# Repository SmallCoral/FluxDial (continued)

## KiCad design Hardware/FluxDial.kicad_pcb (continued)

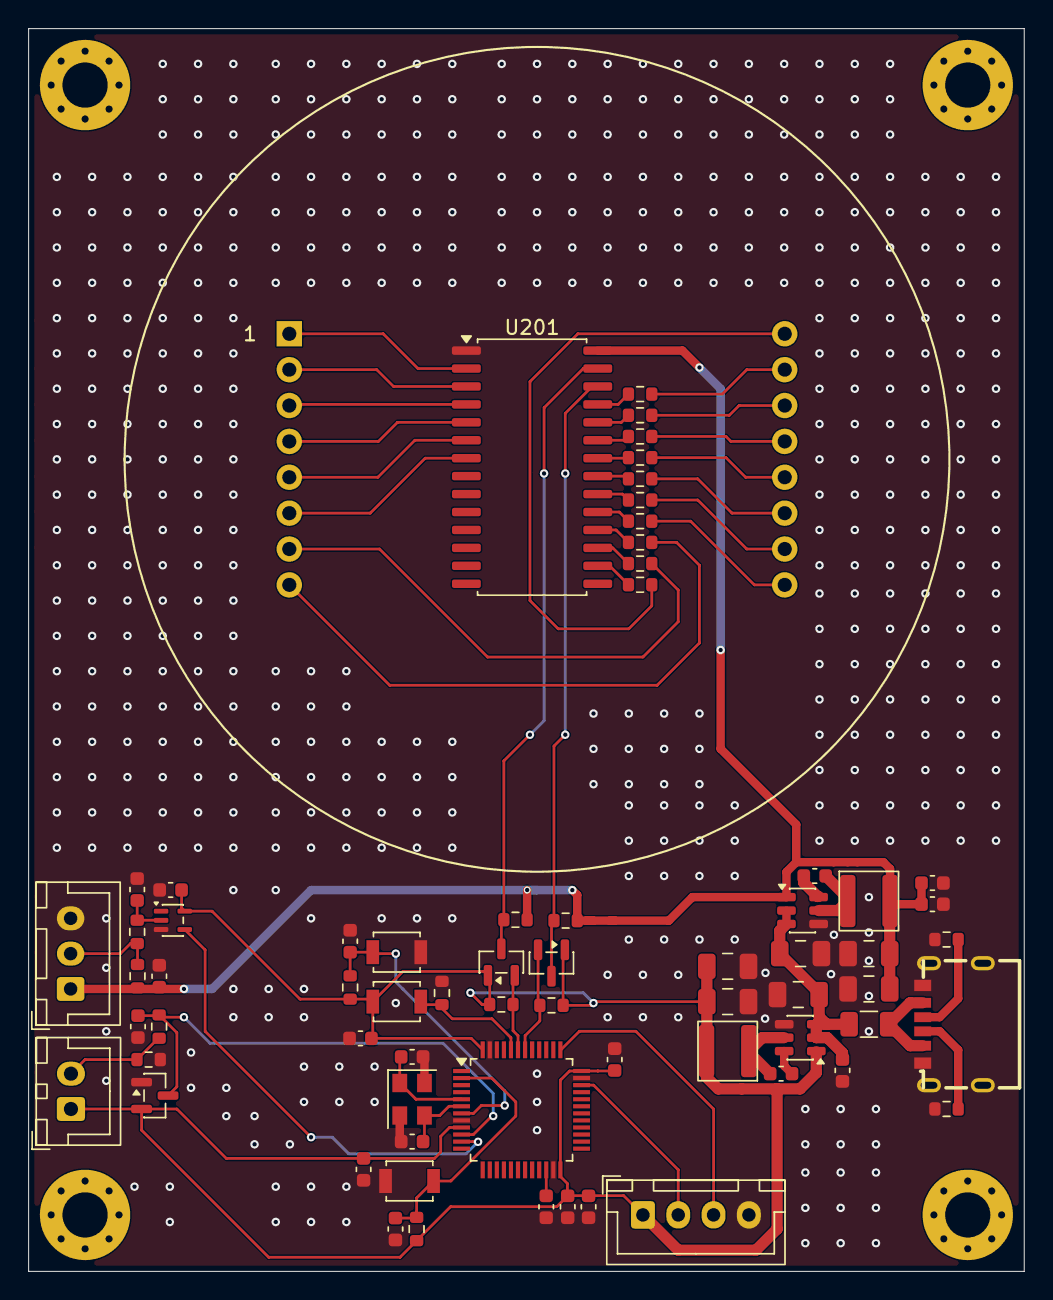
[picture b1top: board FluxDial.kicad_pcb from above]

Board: 2 copper layers, 70.5 x 88.0 mm, 68 parts (0 on the bottom side), 54 nets.

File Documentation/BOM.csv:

位号,数量,参数/型号,KiCad封装,采购与核对要求
J101,1,SHOU HAN TYPE-C 6P(073),FluxDial:Connector_USB__SHOU_HAN_TYPE-C-6P-073_C668623,SHOU HAN TYPE-C 6P(073)；LCSC C668623；仅供电无D+/D−；5V/3A资料额定；四个外侧椭圆屏蔽壳焊盘；无中间圆形定位孔；禁止从J101输入12V
J102,1,SWD / XH 2.50mm,FluxDial:Connector_JST__JST_XH_B4B-XH-A_1x04_P2.50mm_Vertical,JST B4B-XH-A立式4P；1=VREF/3.3V、2=SWDIO、3=SWCLK、4=GND；VREF仅作目标电压检测；接口不含NRST
F101,1,0.5A / 24V 保持电流,FluxDial:Fuse__Fuse_1206_3216Metric,Littelfuse 1206L050/24WR 或等效；保持电流0.5A；最大工作电压至少24V；核对温度降额
U101,1,AP63203WU-7,FluxDial:Package_TO_SOT_SMD__SOT-23-6,Diodes AP63203WU-7；固定3.3V；TSOT26；输入3.8～32V；靠近L101/C102/C106/C103/C105布局
U102,1,AP63205WU-7,FluxDial:Package_TO_SOT_SMD__SOT-23-6,Diodes AP63205WU-7；固定5V；TSOT26；输入3.8～32V；5V输入时工作于低压差模式；靠近L102/C110/C109/C107/C108布局
L101,1,3.9u / SWPA4030S3R9MT,FluxDial:Inductor_Sunlord_SWPA4030S,屏蔽功率电感；Isat最小3.0A；DCR最大74mΩ；用于3.3V DCDC
L102,1,4.7u / SWPA4030S4R7MT,FluxDial:Inductor_Sunlord_SWPA4030S,屏蔽功率电感；Isat最小2.9A；DCR最大78mΩ；用于5V DCDC
C101,1,100n / 25V,FluxDial:Capacitor_SMD__C_0603_1608Metric,0603英制/1608公制；≥25V；X7R；10%；输入高频旁路
"C102,C110",2,10u / 35V,FluxDial:Capacitor_SMD__C_1206_3216Metric,1206英制/3216公制；≥35V；X7R；10%；每路DCDC各一只就近输入储能；核对12V偏压下有效容量
"C103,C105,C107,C108",4,22u / 10V,FluxDial:Capacitor_SMD__C_1206_3216Metric,1206英制/3216公制；≥10V；X7R；10%；每路DCDC各两只；核对偏压下有效容量
"C106,C109",2,100n,FluxDial:Capacitor_SMD__C_0603_1608Metric,0603英制/1608公制；≥25V；X7R；DCDC自举电容，紧贴BST与SW引脚
"R101,R102",2,5.1k 1%,FluxDial:Resistor_SMD__R_0603_1608Metric,0603英制/1608公制；1%；额定功率≥0.1W
SW101,1,启动（BOOT）,FluxDial:Button_Switch_SMD__SW_SPST_B3U-1000P,Omron B3U-1000P；LCSC C231329；3.0×2.5mm；高1.6mm；常开瞬时
"R103,R104,R303,R305",4,10k,FluxDial:Resistor_SMD__R_0603_1608Metric,0603英制/1608公制；1%；额定功率≥0.1W
SW102,1,复位（RESET）,FluxDial:Button_Switch_SMD__SW_SPST_B3U-1000P,Omron B3U-1000P；LCSC C231329；3.0×2.5mm；高1.6mm；常开瞬时
"C104,C201,C301,C303,C304,C305",6,100n,FluxDial:Capacitor_SMD__C_0603_1608Metric,0603英制/1608公制；≥10V；X5R/X7R；10%；核对直流偏压下有效容量
U201,1,HT16K33 / SOP28,FluxDial:Package_SO__SOIC-28W_7.5x17.9mm_P1.27mm,Holtek HT16K33，28脚SOP，依据Rev1.10；不要买20/24脚版本
DS201,1,5858-1DRWB-10,FluxDial:ALS5858_1DRWB_10,原文档5858-1DRWB-10；排距35.08mm/针距2.54mm；孔径和正面方向待实物确认；A2焊盘1.8mm、钻孔1.0mm，孔径待实物核对
"R201,R202,R203,R204,R205,R206,R207,R208,R209,R210",10,330R,FluxDial:Resistor_SMD__R_0603_1608Metric,0603英制/1608公制；1%；额定功率≥0.1W
"Q201,Q202",2,BSS138,FluxDial:Package_TO_SOT_SMD__SOT-23,BSS138；SOT-23；1=G、2=S、3=D
"R211,R212,R213,R214,R304",5,4.7k,FluxDial:Resistor_SMD__R_0603_1608Metric,0603英制/1608公制；1%；额定功率≥0.1W
C202,1,2.2u / 10V,FluxDial:Capacitor_SMD__C_0603_1608Metric,0603英制/1608公制；≥10V；X5R/X7R；10%；核对直流偏压下有效容量
J301,1,NTC 接口 / XH 2.50mm,FluxDial:Connector_JST__JST_XH_B2B-XH-A_1x02_P2.50mm_Vertical,JST B2B-XH-A，2.50mm；须核对供应商XHB线束配套
R301,1,49.9k 0.1%,FluxDial:Resistor_SMD__R_0603_1608Metric,0603英制/1608公制；0.1%精密、低温漂、额定功率≥0.1W
R302,1,1k,FluxDial:Resistor_SMD__R_0603_1608Metric,0603英制/1608公制；1%；额定功率≥0.1W
D301,1,BAV199,FluxDial:Package_TO_SOT_SMD__SOT-23,Nexperia BAV199；1=A1，2=K2，3=K1/A2；不要按其他双二极管脚号替换
J302,1,BTL-004A / XH 2.50mm,FluxDial:Connector_JST__JST_XH_B3B-XH-A_1x03_P2.50mm_Vertical,JST B3B-XH-A，2.50mm；须核对红/黄/白针序及插壳
C302,1,1n,FluxDial:Capacitor_SMD__C_0603_1608Metric,0603英制/1608公制；≥10V；C0G或X7R；5%
U301,1,SN74LVC1G17DCKR,FluxDial:Package_TO_SOT_SMD__SOT-353_SC-70-5,TI SN74LVC1G17DCKR；SC70-5；3.3V供电、5.5V容许输入
SW301,1,单位切换,FluxDial:Button_Switch_SMD__SW_SPST_B3U-1000P,Omron B3U-1000P；LCSC C231329；3.0×2.5mm；高1.6mm；常开瞬时
U401,1,STM32C562CET6,FluxDial:STM32C562CET6_LQFP48_ST,ST STM32C562CET6；512KB闪存/128KB SRAM；LQFP48，本体7×7mm、脚距0.5mm；焊盘按DS14927图42：1.20×0.30mm
"C401,C402,C403",3,100n,FluxDial:Capacitor_SMD__C_0603_1608Metric,0603英制/1608公制；≥10V；X5R/X7R；10%；分别靠近U401的24/36/48脚；核对偏压下有效容量
C404,1,4.7u / 10V,FluxDial:Capacitor_SMD__C_0603_1608Metric,0603英制/1608公制；≥10V；X5R/X7R；10%；MCU总去耦；核对偏压下有效容量
C405,1,2.2u / 10V,FluxDial:Capacitor_SMD__C_0603_1608Metric,0603英制/1608公制；≥10V；X5R/X7R；3MHz时ESR＜20mΩ，采购须核对阻抗曲线；仅用于VCAP，靠近U401-22
C406,1,100n,FluxDial:Capacitor_SMD__C_0603_1608Metric,0603英制/1608公制；≥10V；X5R/X7R；10%；VREF旁路，靠近U401的9/8脚；核对偏压下有效容量
Y401,1,24MHz / CL=10pF,FluxDial:Abracon_ABM8_3.2x2.5mm,Abracon ABM8-24.000MHZ-10-D2Y-T；基频、CL10pF、ESR≤50Ω、C0≤3pF、驱动≤100uW；-40～85℃；1/3晶体端、2/4接地
"C407,C408",2,12p / C0G,FluxDial:Capacitor_SMD__C_0603_1608Metric,0603英制/1608公制；C0G；≥25V；建议±0.5pF；HSE负载电容初值12pF，最终按实际杂散和频偏校准
